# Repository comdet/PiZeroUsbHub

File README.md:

# PiZeroUsbHub
Note!!! Beware restrict area under usb port, you should edit track to avoid them or you master in soldering skill to make non-contact track between GND and 5V

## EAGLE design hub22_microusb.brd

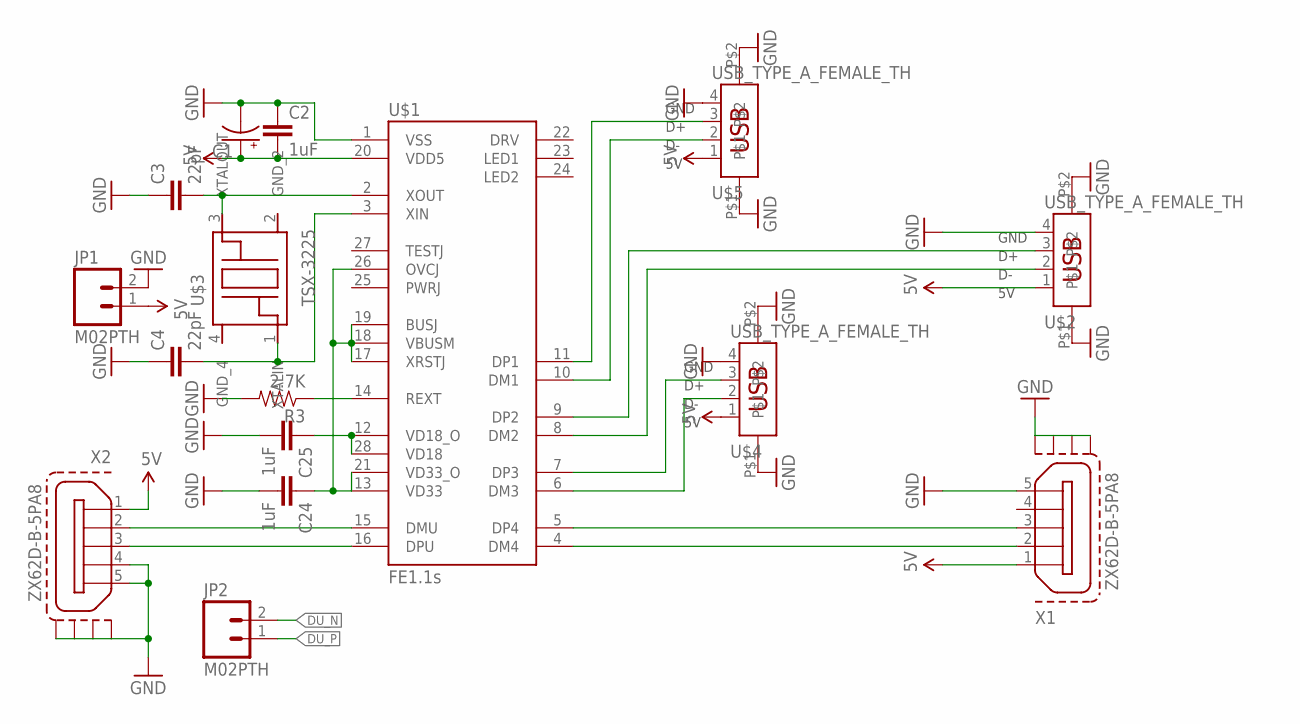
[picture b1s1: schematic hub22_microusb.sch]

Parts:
C1: CAP_POLD; PANASONIC_D
C2, C24, C25: 1uF; 0805
C3, C4: 22pF; 0805
JP1, JP2: M02PTH; 1X02
R3: 2.7K; 0805
U$1: FE1.1S; FE1.1S_SSOP-28
U$2, U$4, U$5: USB_TYPE_A_FEMALE_TH
U$3: TSX-3225
X1, X2: ZX62D-B-5PA8

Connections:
5V: C1.+, C2.2, JP1.1, U$1.20 (VDD5), U$2.1, U$4.1, U$5.1, X1.1, X2.1
DU_N: JP2.2, U$1.15 (DMU), X2.2
DU_P: JP2.1, U$1.16 (DPU), X2.3
GND: C1.-, C2.1, C3.1, C4.1, C24.2, C25.2, JP1.2, R3.2, U$1.1 (VSS), U$2.4, U$2.P$1, U$2.P$2, U$4.4, U$4.P$1, U$4.P$2, U$5.4, U$5.P$1, U$5.P$2, X1.5, X1.S1, X1.S2, X1.S3, X1.S4, X2.4, X2.5, X2.S1, X2.S2, X2.S3, X2.S4
unnamed: C3.2, U$1.2 (XOUT), U$3.3 (XTALOUT)
unnamed: C4.2, U$1.3 (XIN), U$3.1 (XTALIN)
unnamed: C24.1, U$1.13 (VD33), U$1.17 (XRSTJ), U$1.18 (VBUSM), U$1.19 (BUSJ), U$1.21 (VD33_O), U$1.26 (OVCJ)
unnamed: R3.1, U$1.14 (REXT)
unnamed: U$1.4 (DM4), X1.2
unnamed: U$1.5 (DP4), X1.3
unnamed: U$1.6 (DM3), U$4.2
unnamed: U$1.7 (DP3), U$4.3
unnamed: U$1.8 (DM2), U$2.2
unnamed: U$1.9 (DP2), U$2.3
unnamed: U$1.10 (DM1), U$5.2
unnamed: U$1.11 (DP1), U$5.3
unnamed: C25.1, U$1.12 (VD18_O), U$1.28 (VD18)

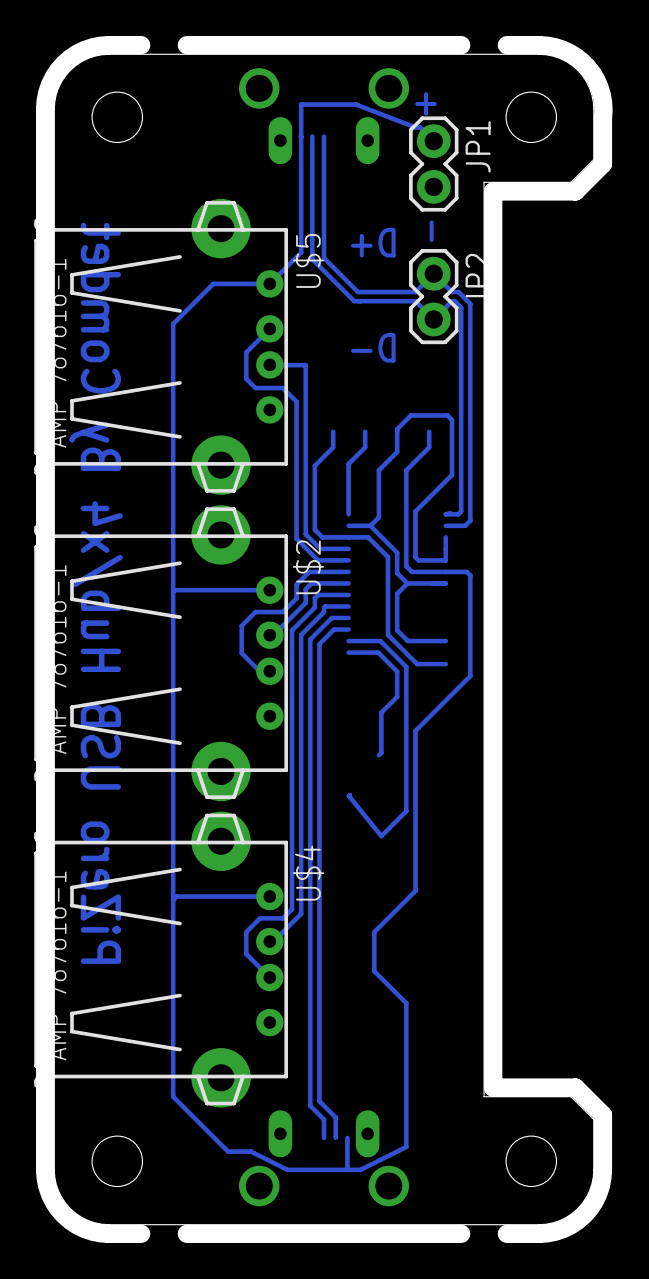
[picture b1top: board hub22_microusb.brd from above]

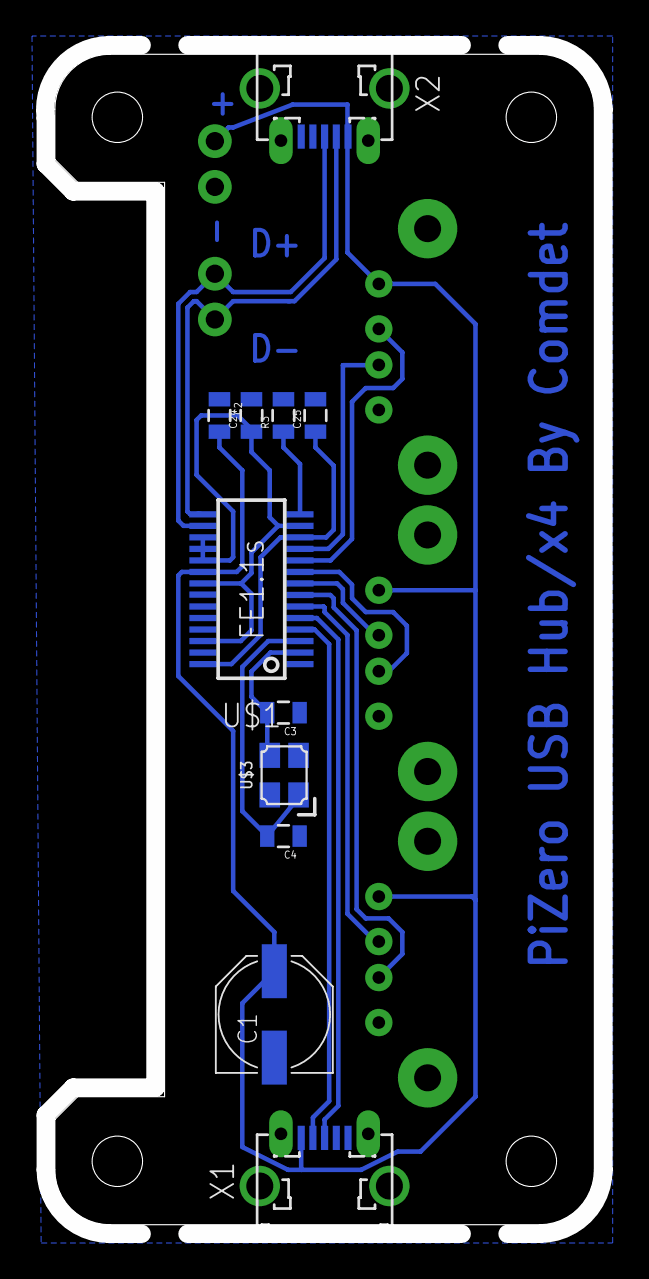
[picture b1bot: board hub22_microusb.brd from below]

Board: 2 copper layers, 31.0 x 66.0 mm, 16 parts (11 on the bottom side), 17 nets.

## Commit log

2016-11-01 :circus_tent: Added .gitattributes & .gitignore files

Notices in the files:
parts and their libraries:
SparkFun-Capacitors: Licensing: Creative Commons ShareAlike 4.0 International - https://creativecommons.org/licenses/by-sa/4.0
